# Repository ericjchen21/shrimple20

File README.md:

# Shrimple20 Keypad - December 2025

The final project for my Electronic Circuit Applications class, the Shrimple20 Keypad, a 20 Key programmable macropad using KMK firmware on the Adafruit KB2040 with Kailh Choc V1 Switches

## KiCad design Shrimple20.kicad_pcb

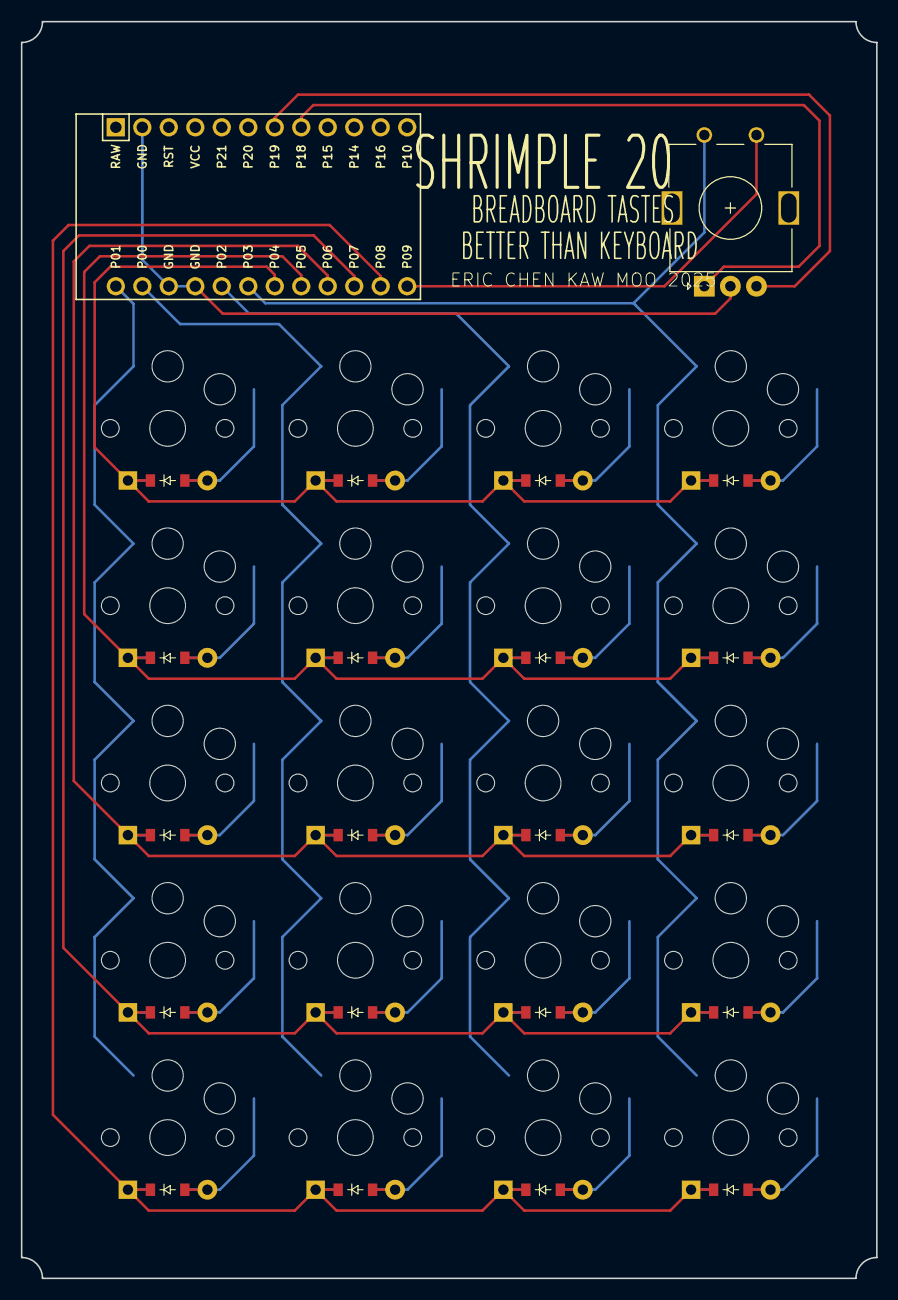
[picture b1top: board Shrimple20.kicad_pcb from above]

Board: 2 copper layers, 82.0 x 120.5 mm, 42 parts (0 on the bottom side), 33 nets.

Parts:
D1, D2, D3, D4, D5, D6, D7, D8, D9, D10, D11, D12, D13, D14, D15, D16, D17, D18, D19, D20: ComboDiode
MCU1: ProMicro
ROT1: rotary_encoder
S1, S2, S3, S4, S5, S6, S7, S8, S9, S10, S11, S12, S13, S14, S15, S16, S17, S18, S19, S20: PG1350

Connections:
GND: MCU1.2, MCU1.15, MCU1.16, ROT1.C
P0: MCU1.14, S6.1, S7.1, S8.1, S9.1, S10.1
P1: MCU1.13, S1.1, S2.1, S3.1, S4.1, S5.1
P2: MCU1.17, S11.1, S12.1, S13.1, S14.1, S15.1
P3: MCU1.18, ROT1.1, S16.1, S17.1, S18.1, S19.1, S20.1
P4: D5.1, D10.1, D15.1, D20.1, MCU1.19
P5: D4.1, D9.1, D14.1, D19.1, MCU1.20
P6: D3.1, D8.1, D13.1, D18.1, MCU1.21
P7: D2.1, D7.1, D12.1, D17.1, MCU1.22
P8: D1.1, D6.1, D11.1, D16.1, MCU1.23
P9: MCU1.24, ROT1.2
P18: MCU1.8, ROT1.A
P19: MCU1.7, ROT1.B
col1_row1: D1.2, S1.2
col1_row2: D2.2, S2.2
col1_row3: D3.2, S3.2
col1_row4: D4.2, S4.2
col1_row5: D5.2, S5.2
col2_row1: D6.2, S6.2
col2_row2: D7.2, S7.2
col2_row3: D8.2, S8.2
col2_row4: D9.2, S9.2
col2_row5: D10.2, S10.2
col3_row1: D11.2, S11.2
col3_row2: D12.2, S12.2
col3_row3: D13.2, S13.2
col3_row4: D14.2, S14.2
col3_row5: D15.2, S15.2
col4_row1: D16.2, S16.2
col4_row2: D17.2, S17.2
col4_row3: D18.2, S18.2
col4_row4: D19.2, S19.2
col4_row5: D20.2, S20.2

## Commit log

2026-01-06 Initialize README with project details
    Add project description for Shrimple20 Keypad.
2026-01-06 Update README formatting and project description
